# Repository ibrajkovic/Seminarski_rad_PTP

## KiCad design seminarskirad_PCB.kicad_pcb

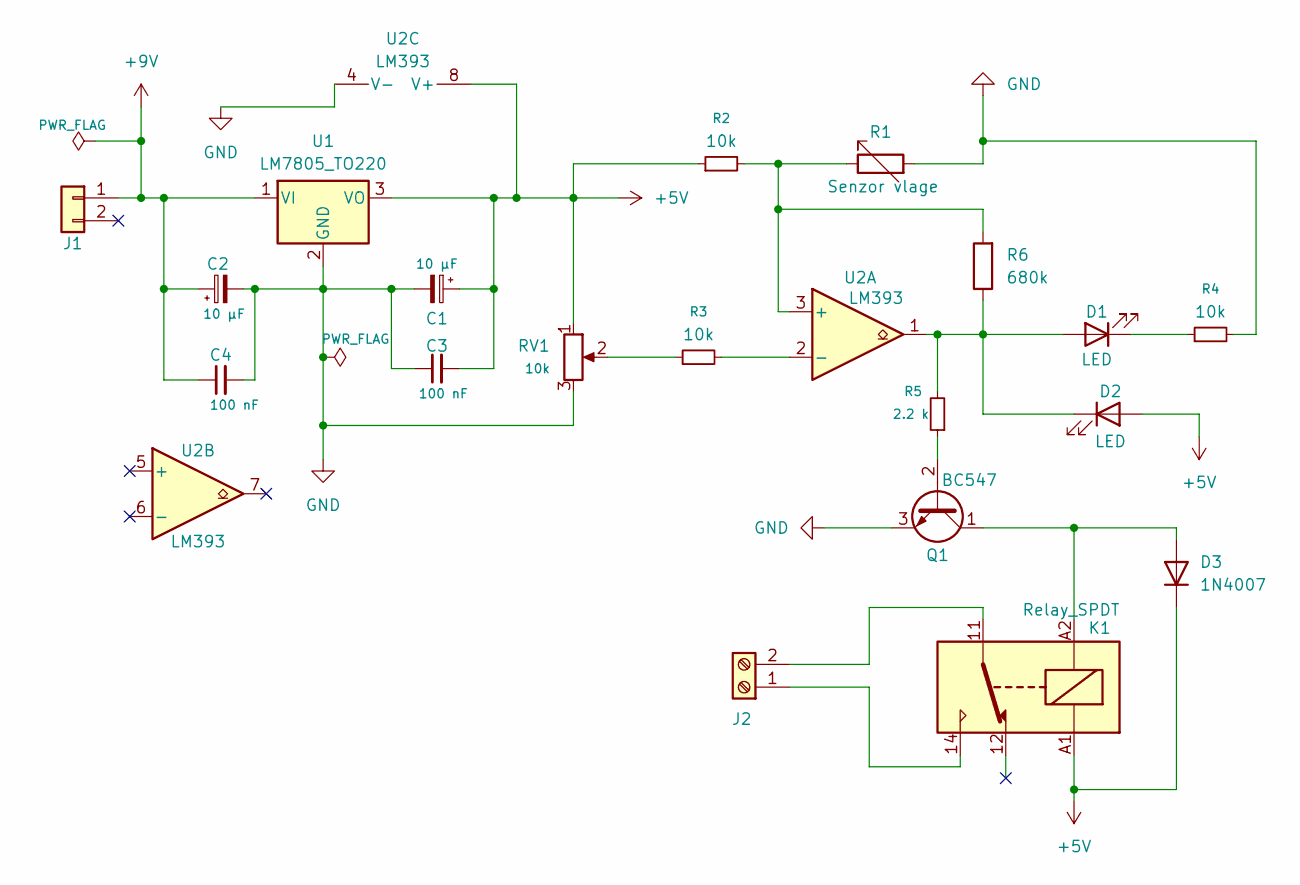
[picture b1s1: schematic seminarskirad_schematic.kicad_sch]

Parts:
C1, C2: 10 µF; CP_Radial_D5.0mm_P2.50mm; ManufacturerPartNumber EEU-FC1C100
C3: 100 nF; C_Disc_D5.0mm_W2.5mm_P2.50mm; ManuafcturerPartNumber C0805C104K5RACTU
C4: 100 nF; C_Disc_D5.0mm_W2.5mm_P2.50mm; ManufacturerPartNumber C0805C104K5RACTU
D1, D2: LED; LED_D5.0mm; ManufacturerPartNumber Kingbright WP710A10ID/LID
D3: 1N4007; D_DO-41_SOD81_P10.16mm_Horizontal; ManufacturerPartNumber 1N4007
J1: Conn_01x02; PinHeader_1x02_P2.54mm_Vertical; ManufacturerPartNumber Phoenix Contact
J2: Screw_Terminal_01x02; PinHeader_1x02_P2.54mm_Vertical; ManufacturerPartNumber Phoenix Contact
K1: Relay_SPDT; Relay_SPDT_CUI_SR5; ManufacturerPartNumber SRD-05VDC-SL-C
Q1: BC547; TO-92_Inline; ManufacturerPartNumber BC547C
R1: Senzor vlage; PinHeader_1x02_P2.54mm_Vertical
R2, R3, R4: 10k; R_Axial_DIN0207_L6.3mm_D2.5mm_P7.62mm_Horizontal; ManufacturerPartNumber CFR-25JB-52-10K
R5: 2.2 k; R_Axial_DIN0207_L6.3mm_D2.5mm_P7.62mm_Horizontal; ManufacturerPartNumber CFR-25JB-52-2K2
R6: 680k; R_Axial_DIN0207_L6.3mm_D2.5mm_P7.62mm_Horizontal; ManufacturerPartNumber CFR-25JB-52-680K
RV1: 10k; Potentiometer_ACP_CA9-H5_Horizontal; ManufacturerPartNumber PTV09A-4020F-B103
U1: LM7805_TO220; TO-220-3_Vertical; ManufactorerPartNumber LM7805CT
U2: LM393; DIP-8_W7.62mm; ManufacturerPartNumber LM393Pv

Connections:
+5V: C1.1, C3.2, D2.2 (A), D3.1 (K), K1.A1, R2.1, RV1.1, U1.3 (VO), U2.8 (V+)
+9V: C2.1, C4.1, J1.1, U1.1 (VI)
GND: C1.2, C2.2, C3.1, C4.2, Q1.3 (E), R1.2, R4.2, RV1.3, U1.2 (GND), U2.4 (V-)
unnamed: D1.2 (A), D2.1 (K), R5.2, R6.1, U2.1
unnamed: D1.1 (K), R4.1
unnamed: D3.2 (A), K1.A2, Q1.1 (C)
unnamed: J2.1, K1.14
unnamed: J2.2, K1.11
unnamed: Q1.2 (B), R5.1
unnamed: R3.1, RV1.2
unnamed: R1.1, R2.2, R6.2, U2.3 (+)
unnamed: R3.2, U2.2 (-)

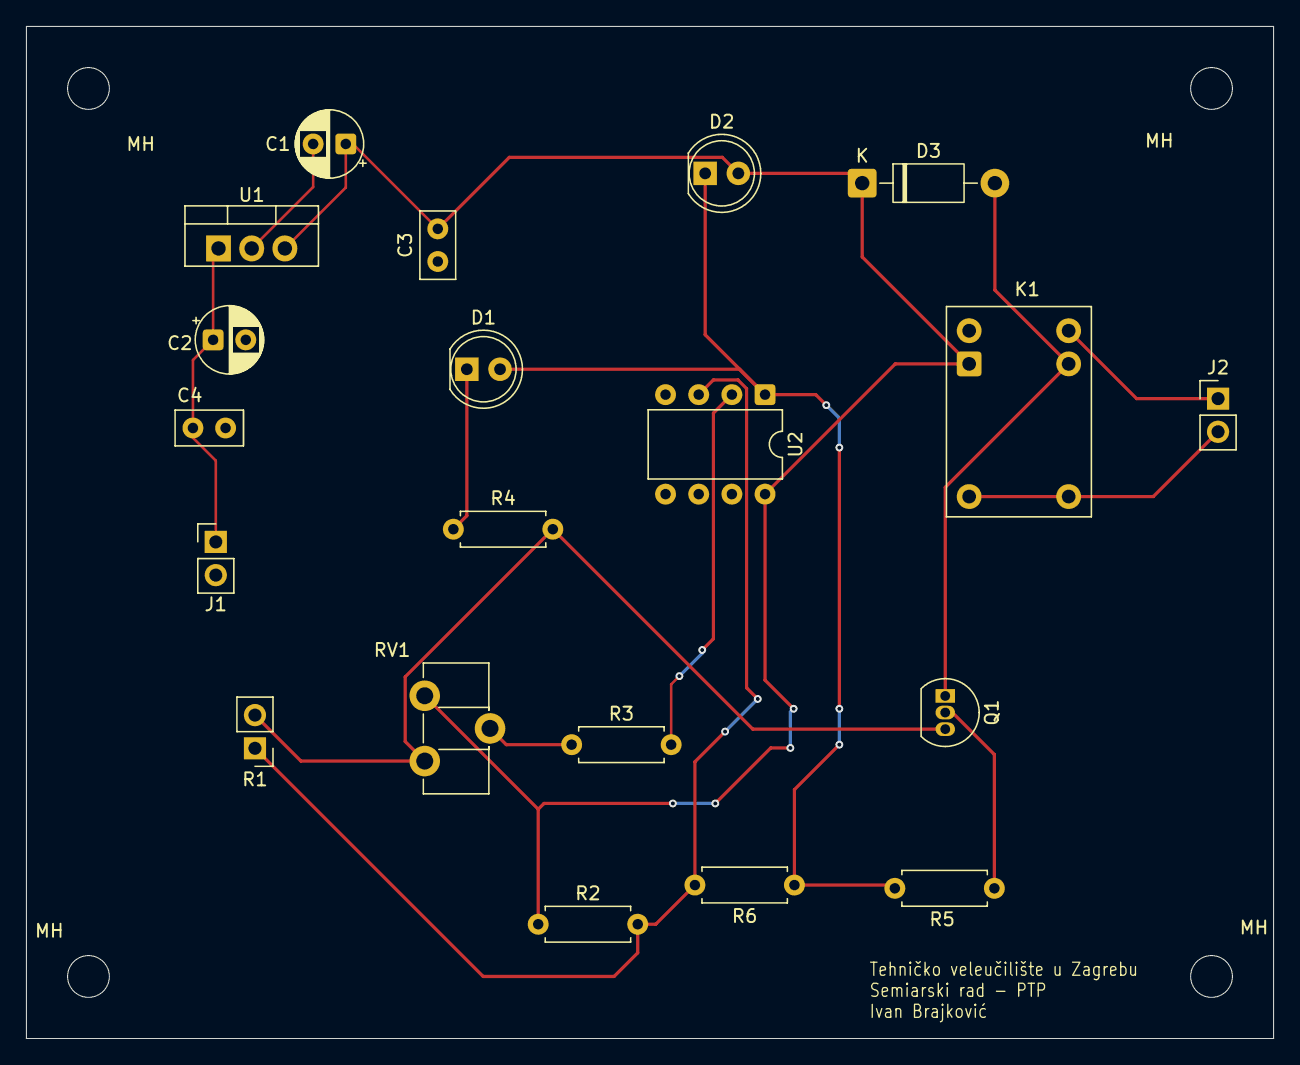
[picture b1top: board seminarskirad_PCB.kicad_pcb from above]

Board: 2 copper layers, 95.5 x 77.5 mm, 24 parts (0 on the bottom side), 12 nets.

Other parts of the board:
MH: MountingHole_3.2mm_M3
MH#2, MH#3, MH#4: MountingHole_3.2mm_M3

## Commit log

2026-06-28 Dodatni fileovi
2026-06-28 Dodatan file
